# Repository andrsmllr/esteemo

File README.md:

# esteemo
An educational micro-controller board for the electrotechnically challenged.

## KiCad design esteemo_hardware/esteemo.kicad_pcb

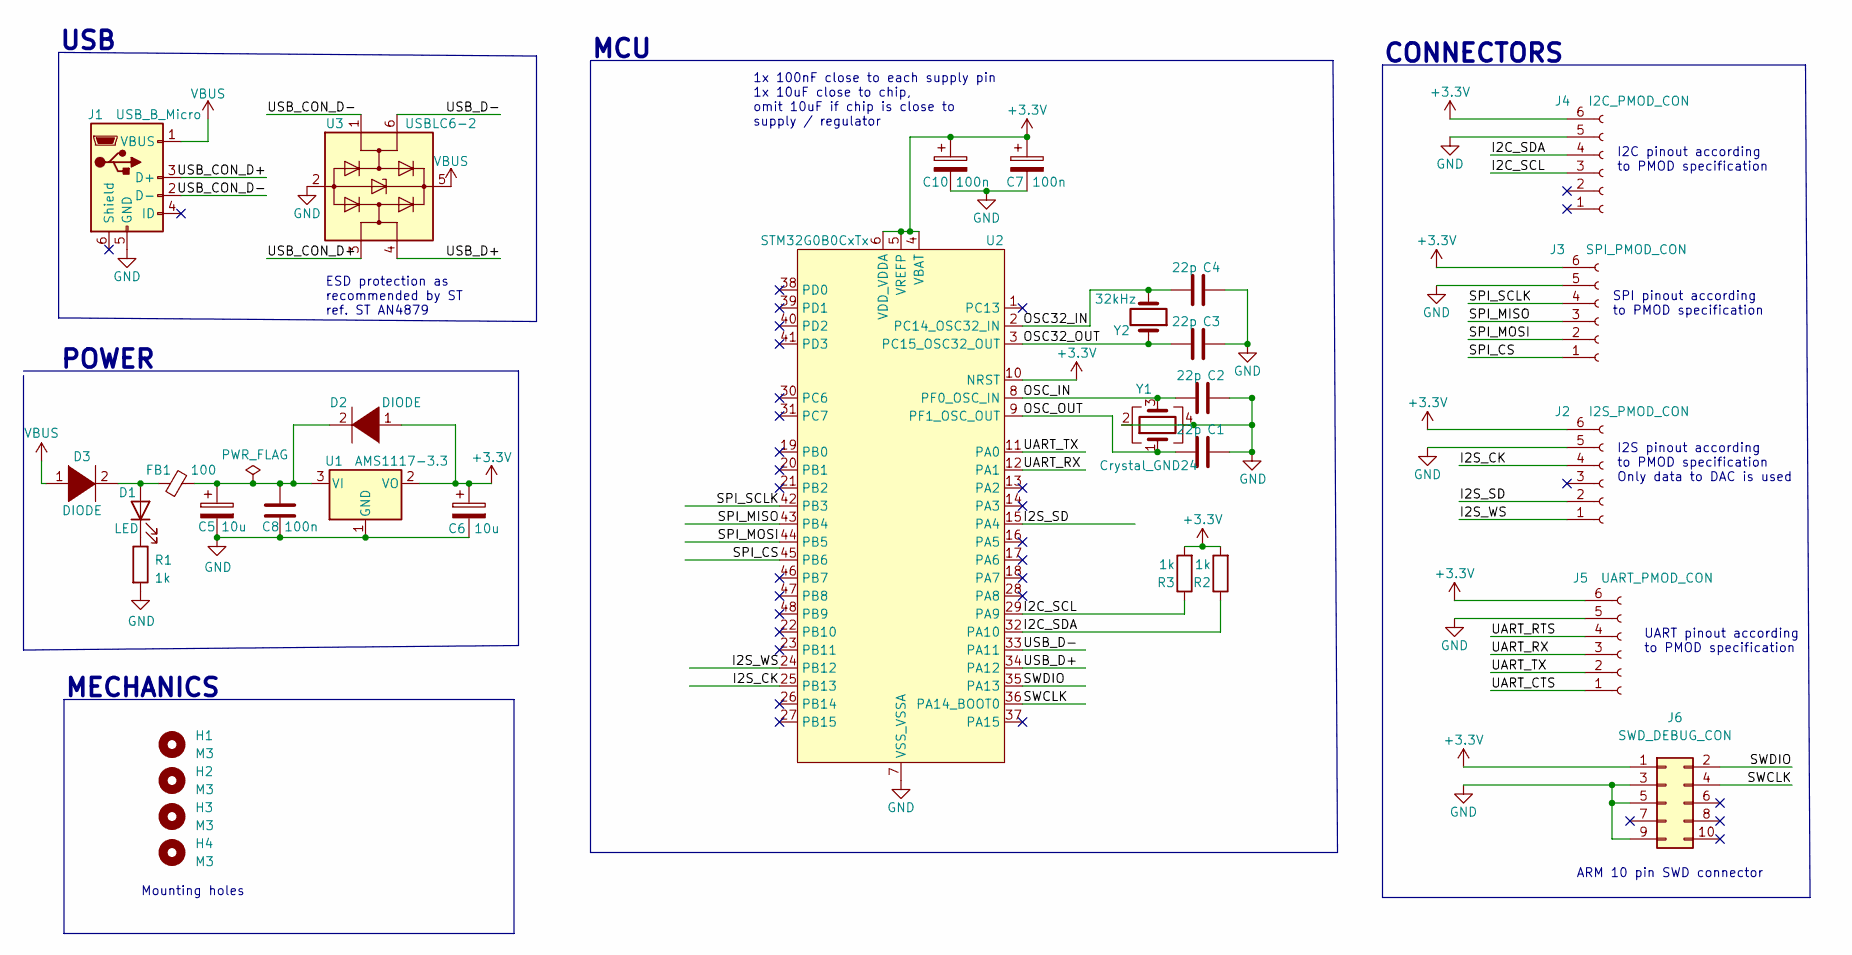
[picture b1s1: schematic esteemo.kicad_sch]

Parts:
C1, C2, C3, C4: 22p; C_0805_2012Metric; LCSC_MPN C1804
C5, C6: 10u; CP_EIA-3216-18_Kemet-A; LCSC_MPN C7171
C7, C8, C10: 100n; C_0805_2012Metric; LCSC_MPN C7173
D1: LED; D_1206_3216Metric; LCSC_MPN C93133
D2, D3: DIODE; D_SOD-323; LCSC_MPN C146335
FB1: 100; R_0805_2012Metric; LCSC_MPN C1017
H1, H2, H3, H4: M3; MountingHole_3.2mm_M3
J1: USB_B_Micro; USB_Micro-B_Amphenol_10104110_Horizontal; LCSC_MPN C132563
J2: I2S_PMOD_CON; PinHeader_1x06_P2.54mm_Vertical; LCSC_MPN C718239
J3: SPI_PMOD_CON; PinHeader_1x06_P2.54mm_Vertical; LCSC_MPN C718239
J4: I2C_PMOD_CON; PinHeader_1x06_P2.54mm_Vertical; LCSC_MPN C718239
J5: UART_PMOD_CON; PinHeader_1x06_P2.54mm_Vertical; LCSC_MPN C718239
J6: SWD_DEBUG_CON; PinHeader_2x05_P1.27mm_Vertical; LCSC_MPN C239059
R1, R2, R3: 1k; R_0805_2012Metric; LCSC_MPN C17513
U1: AMS1117-3.3; SOT-223; LCSC_MPN C6186
U2: STM32G0B0CxTx; LQFP-48_7x7mm_P0.5mm; LCSC_MPN C529329
U3: USBLC6-2; SOT-23-6; LCSC_MPN C7519
Y1: Crystal_GND24; Crystal_SMD_2016-4Pin_2.0x1.6mm; LCSC_MPN C648933
Y2: 32kHz; Crystal_SMD_3215-2Pin_3.2x1.5mm; LCSC_MPN C32346

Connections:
+3.3V: C6.1, C7.1, C10.1, D2.1 (K), J2.6, J3.6, J4.6, J5.6, J6.1, R2.2, R3.2, U1.2 (VO), U2.4 (VBAT), U2.5 (VREFP), U2.6 (VDD_VDDA), U2.10 (NRST)
/I2C_SCL: J4.3, R3.1, U2.29 (PA9)
/I2C_SDA: J4.4, R2.1, U2.32 (PA10)
/I2S_CK: J2.4, U2.25 (PB13)
/I2S_SD: J2.2, U2.15 (PA4)
/I2S_WS: J2.1, U2.24 (PB12)
/OSC32_IN: C4.2, U2.2 (PC14_OSC32_IN), Y2.2
/OSC32_OUT: C3.2, U2.3 (PC15_OSC32_OUT), Y2.1
/OSC_IN: C2.2, U2.8 (PF0_OSC_IN), Y1.3
/OSC_OUT: C1.2, U2.9 (PF1_OSC_OUT), Y1.1
/SPI_CS: J3.1, U2.45 (PB6)
/SPI_MISO: J3.3, U2.43 (PB4)
/SPI_MOSI: J3.2, U2.44 (PB5)
/SPI_SCLK: J3.4, U2.42 (PB3)
/SWCLK: J6.4, U2.36 (PA14_BOOT0)
/SWDIO: J6.2, U2.35 (PA13)
/UART_CTS: J5.1
/UART_RTS: J5.4
/UART_RX: J5.3, U2.12 (PA1)
/UART_TX: J5.2, U2.11 (PA0)
/USB_CON_D+: J1.3 (D+), U3.3 (I/O2)
/USB_CON_D-: J1.2 (D-), U3.1 (I/O1)
/USB_D+: U2.34 (PA12), U3.4 (I/O2)
/USB_D-: U2.33 (PA11), U3.6 (I/O1)
GND: C1.1, C2.1, C3.1, C4.1, C5.2, C6.2, C7.2, C8.2, C10.2, J1.5 (GND), J2.5, J3.5, J4.5, J5.5, J6.3, J6.5, J6.9, R1.2, U1.1 (GND), U2.7 (VSS_VSSA), U3.2 (GND), Y1.2, Y1.4
unnamed: C5.1, C8.1, D2.2 (A), FB1.2, U1.3 (VI)
unnamed: D1.1 (K), R1.1
unnamed: D1.2 (A), D3.2 (A), FB1.1
VBUS: D3.1 (K), J1.1 (VBUS), U3.5 (VBUS)

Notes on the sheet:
MECHANICS
1x 100nF close to each supply pin 1x 10uF close to chip, omit 10uF if chip is close to supply / regulator
ESD protection as recommended by ST ref. ST AN4879
I2S pinout according to PMOD specification Only data to DAC is used
POWER
CONNECTORS
I2C pinout according to PMOD specification
Mounting holes
SPI pinout according to PMOD specification
MCU
UART pinout according to PMOD specification
USB
ARM 10 pin SWD connector

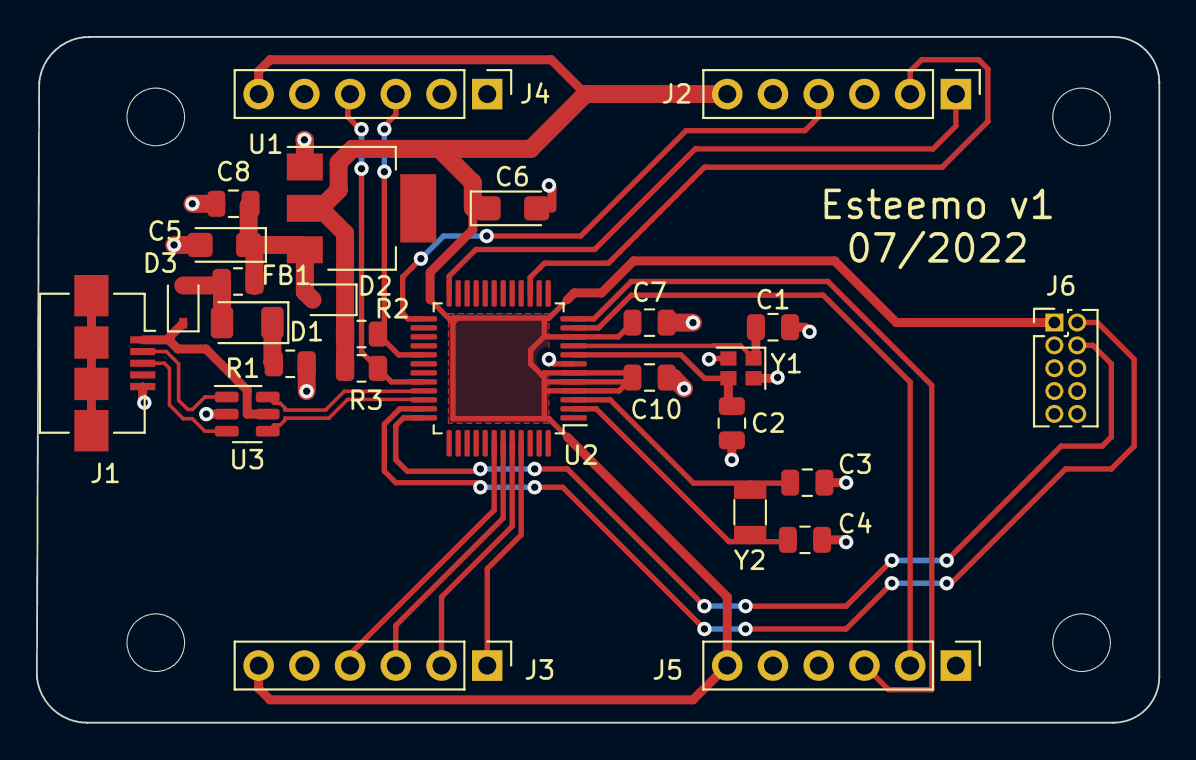
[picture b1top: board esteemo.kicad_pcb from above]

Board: 2 copper layers, 62.4 x 38.1 mm, 31 parts (0 on the bottom side), 27 nets.

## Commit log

2022-07-16 Initial commit adding datasheets and Kicad schematic + layout.
2022-07-16 Add pictore of hardware revision 1.
2022-07-16 Update PCB picture
2022-07-22 Review PCB and prepare ordering
2022-07-22 Update PCB preview image
2023-02-04 Add datasheets.
2023-02-05 Dump local changes.
